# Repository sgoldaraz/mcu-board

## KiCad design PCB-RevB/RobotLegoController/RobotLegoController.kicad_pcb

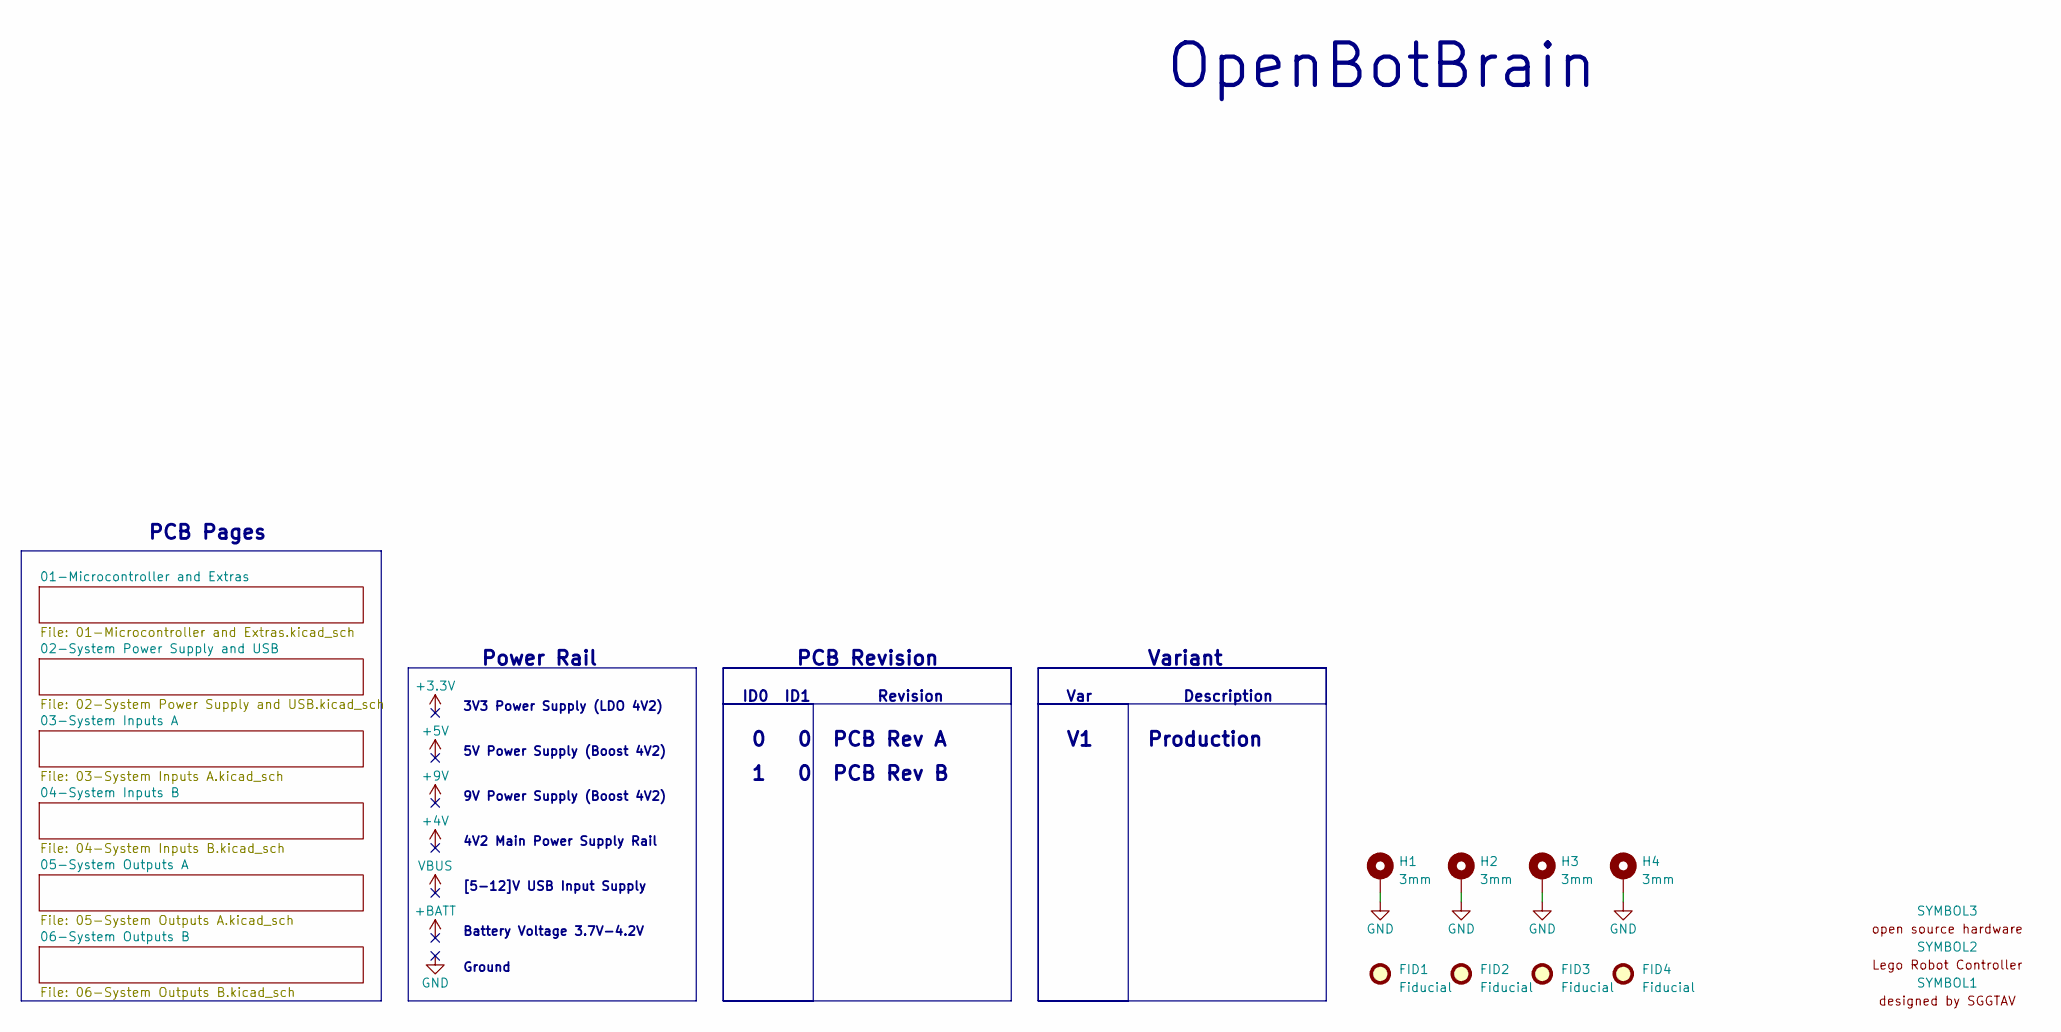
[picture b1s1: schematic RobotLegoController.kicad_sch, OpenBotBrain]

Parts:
FID1, FID2, FID3, FID4: Fiducial; Fiducial_1mm_Mask3mm
H1, H2, H3, H4: 3mm; MountingHole_3.2mm_M3_Pad
SYMBOL1: sggtav_logo
SYMBOL2: lego_robot_controller
SYMBOL3: open_source

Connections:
GND: H1.1, H2.1, H3.1, H4.1; also elsewhere on the board

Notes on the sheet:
Power Rail
Var
0 0
ID0 ID1
9V Power Supply (Boost 4V2)
3V3 Power Supply (LDO 4V2)
Battery Voltage 3.7V-4.2V
PCB Rev B
Variant
[5-12]V USB Input Supply
Description
1 0
Production
PCB Revision
PCB Rev A
4V2 Main Power Supply Rail
Revision
PCB Pages
Ground
5V Power Supply (Boost 4V2)
OpenBotBrain

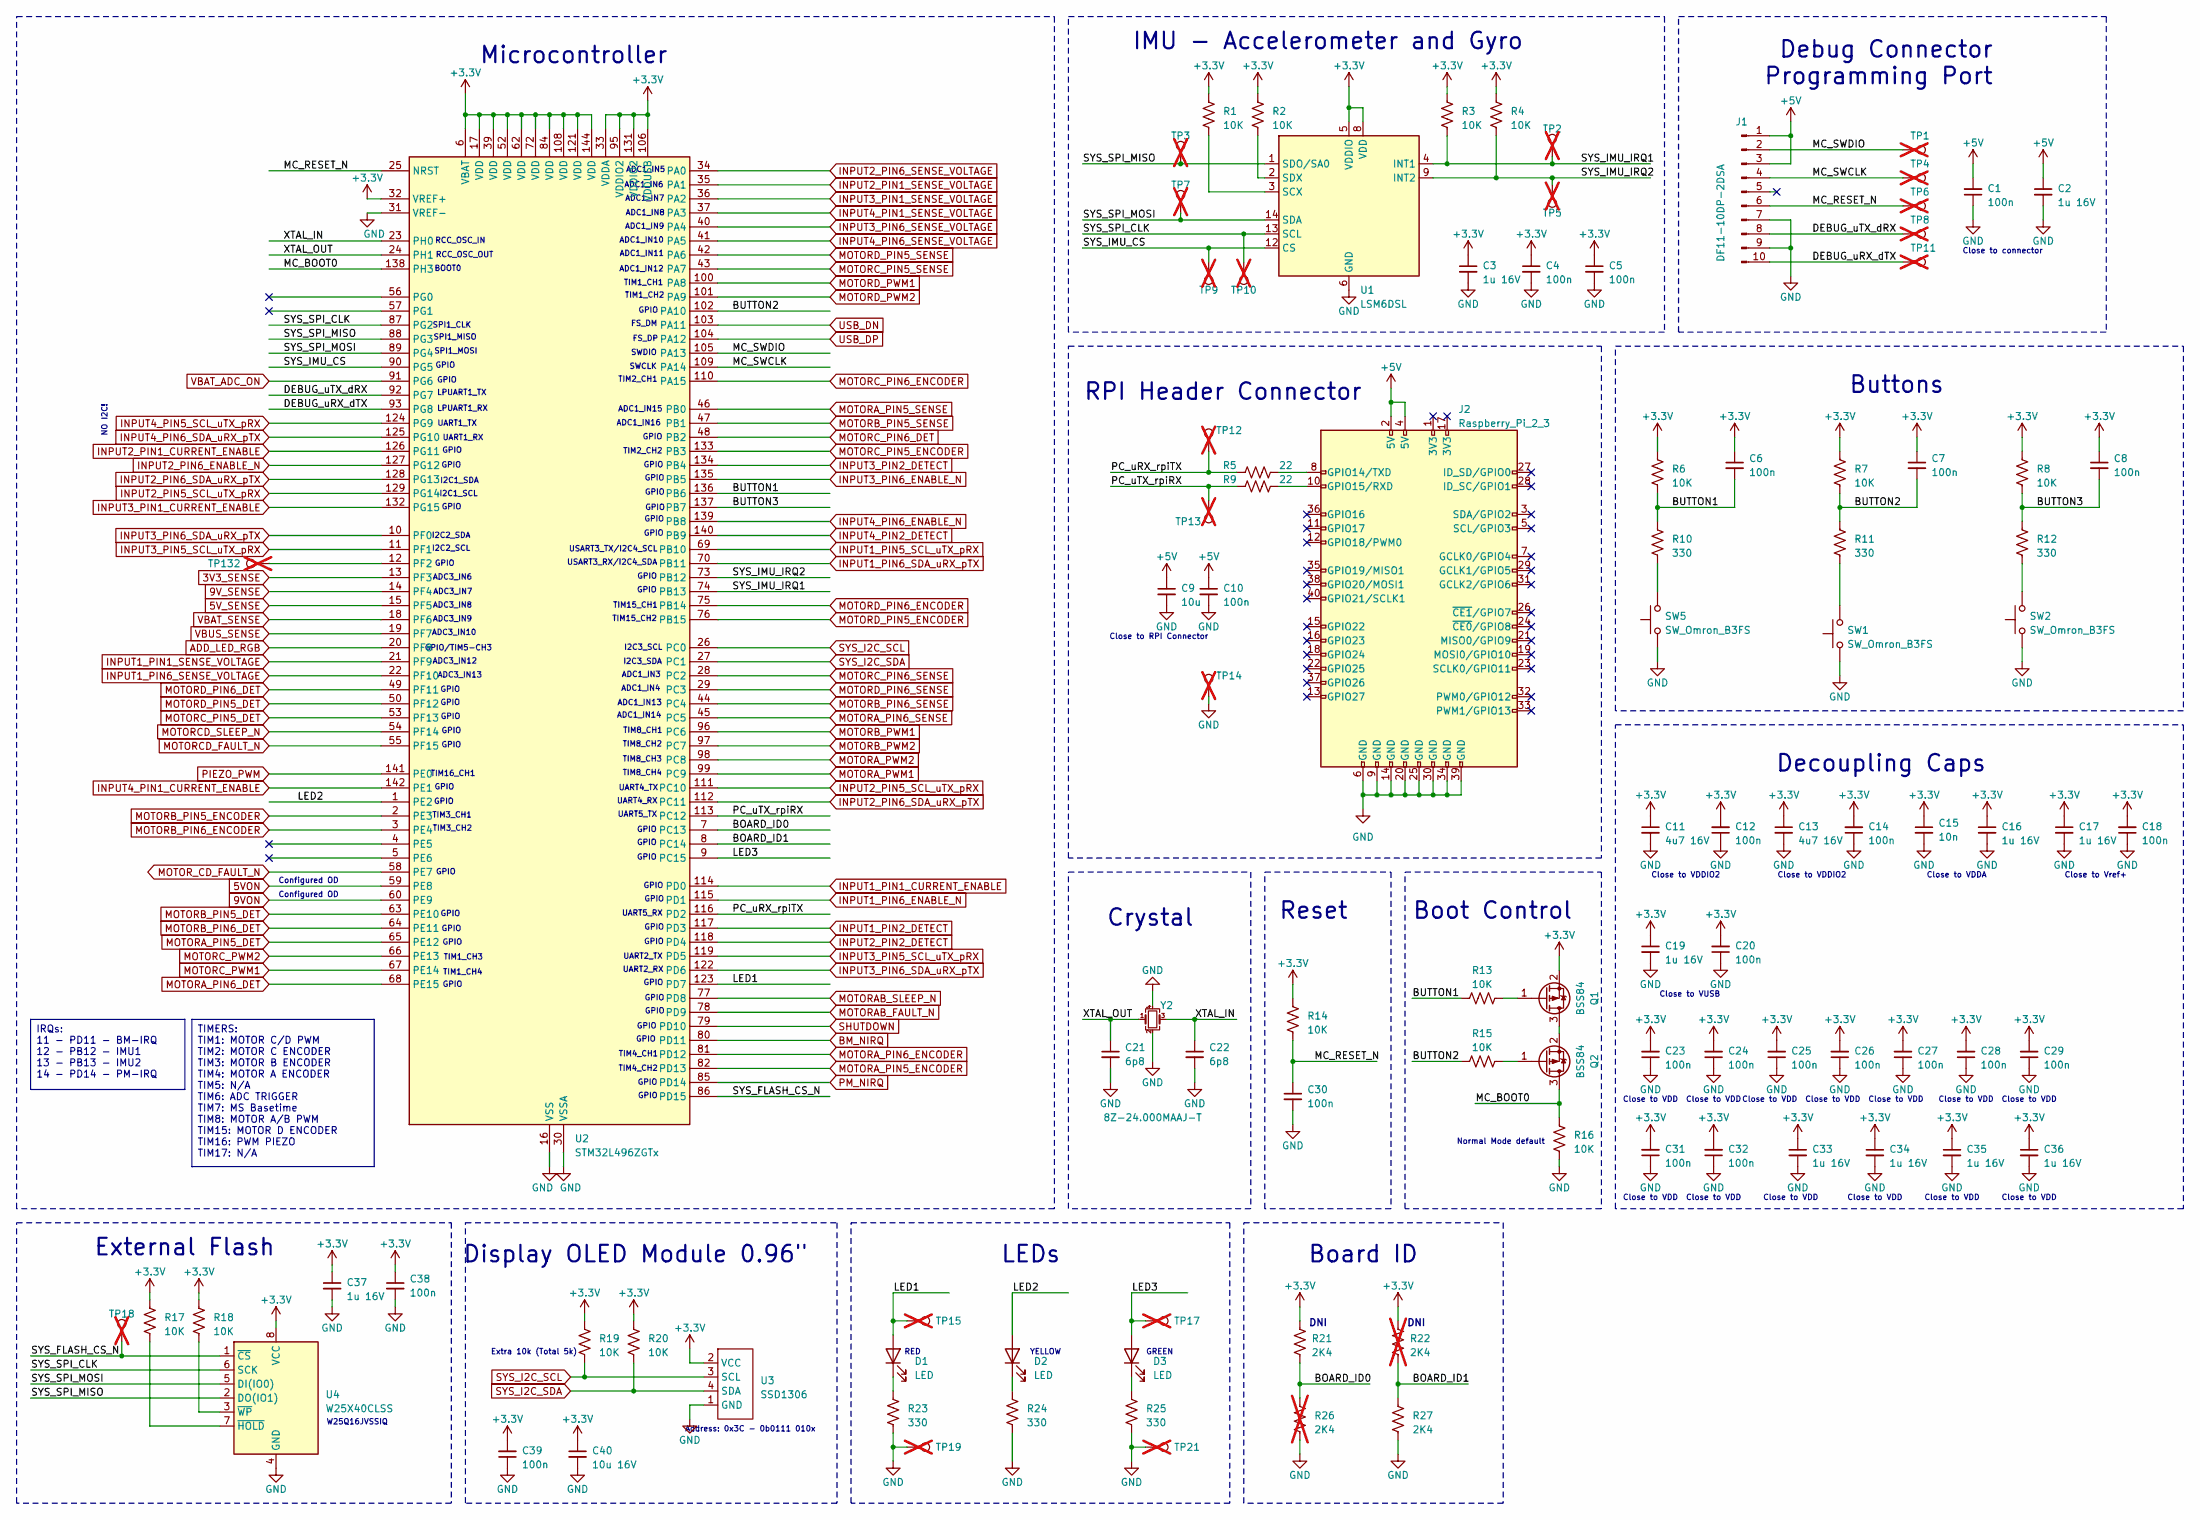
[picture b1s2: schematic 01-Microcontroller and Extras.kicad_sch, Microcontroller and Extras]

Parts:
C1, C4, C5, C6, C7, C8, C10, C12, C14, C18, C20, C23, C24, C25, C26, C27, C28, C29, C30, C31, C32, C38, C39: 100n; C_0402_1005Metric
C2, C3, C16, C17, C19, C33, C34, C35, C36, C37: 1u 16V; C_0603_1608Metric
C9: 10u; C_0805_2012Metric
C11, C13: 4u7 16V; C_0603_1608Metric
C15: 10n; C_0402_1005Metric
C21, C22: 6p8; C_0402_1005Metric
C40: 10u 16V; C_0805_2012Metric
D1, D2, D3: LED; LED_0402_1005Metric
J1: DF11-10DP-2DSA; JST_PHD_B10B-PHDSS_2x05_P2.00mm_Vertical
J2: Raspberry_Pi_2_3; PinHeader_2x20_P2.54mm_Vertical
Q1, Q2: BSS84; SOT-23
R1, R2, R3, R4, R6, R7, R8, R13, R14, R15, R16, R17, R18, R19, R20: 10K; R_0402_1005Metric
R5, R9: 22; R_0402_1005Metric
R10, R11, R12, R23, R24, R25: 330; R_0402_1005Metric
R21, R27: 2K4; R_0402_1005Metric
R22, R26: 2K4; R_0402_1005Metric; not fitted
SW1, SW2, SW5: SW_Omron_B3FS; SW_Push_1P1T_NO_6x6mm_H9.5mm
TP1, TP2, TP3, TP4, TP5, TP6, TP7, TP8, TP9, TP10, TP11, TP12, TP13, TP14, TP18, TP132: S1mm; TestPoint_Pad_1.0x1.0mm; not fitted
TP15, TP17, TP19, TP21: TH1mm; TestPoint_THTPad_1.0x1.0mm_Drill0.5mm; not fitted
U1: LSM6DSL; LGA-14_3x2.5mm_P0.5mm_LayoutBorder3x4y
U2: STM32L496ZGTx; LQFP-144_20x20mm_P0.5mm
U3: SSD1306; 128x64OLED
U4: W25X40CLSS; SOIC-8_5.275x5.275mm_P1.27mm
Y2: 8Z-24.000MAAJ-T; Crystal_SMD_Abracon_ABM10-4Pin_2.5x2.0mm

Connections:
3V3_SENSE: U2.13 (PF3); also elsewhere on the board
5VON: U2.59 (PE8); also elsewhere on the board
5V_SENSE: U2.15 (PF5); also elsewhere on the board
9VON: U2.60 (PE9); also elsewhere on the board
9V_SENSE: U2.14 (PF4); also elsewhere on the board
+3.3V: C3.1, C4.1, C5.1, C6.1, C7.1, C8.1, C11.1, C12.2, C13.1, C14.2, C15.1, C16.1, C17.1, C18.2, C19.1, C20.2, C23.2, C24.2, C25.2, C26.2, C27.2, C28.2, C29.2, C31.2, C32.2, C33.1, C34.1, C35.1, C36.1, C37.1, C38.1, C39.2, C40.1, Q1.2 (S), R1.2, R2.2, R3.2, R4.2, R6.2, R7.2, R8.2, R14.2, R17.2, R18.2, R19.2, R20.2, R21.2, R22.2, U1.5 (VDDIO), U1.8 (VDD), U2.6 (VBAT), U2.17 (VDD), U2.32 (VREF+), U2.33 (VDDA), U2.39 (VDD), U2.52 (VDD), U2.62 (VDD), U2.72 (VDD), U2.84 (VDD), U2.95 (VDDIO2), U2.106 (VDDUSB), U2.108 (VDD), U2.121 (VDD), U2.131 (VDDIO2), U2.144 (VDD), U3.2 (VCC), U4.8 (VCC); also elsewhere on the board
+5V: C1.2, C2.1, C9.1, C10.1, J1.1, J1.3, J2.2 (5V), J2.4 (5V); also elsewhere on the board
/01-Microcontroller and Extras/BOARD_ID0: R21.1, R26.2, U2.7 (PC13)
/01-Microcontroller and Extras/BOARD_ID1: R22.1, R27.2, U2.8 (PC14)
/01-Microcontroller and Extras/BUTTON1: C6.2, R6.1, R10.2, R13.2, U2.136 (PB6)
/01-Microcontroller and Extras/BUTTON2: C7.2, R7.1, R11.2, R15.2, U2.102 (PA10)
/01-Microcontroller and Extras/BUTTON3: C8.2, R8.1, R12.2, U2.137 (PB7)
/01-Microcontroller and Extras/DEBUG_uRX_dTX: J1.10, TP11.1, U2.93 (PG8)
/01-Microcontroller and Extras/DEBUG_uTX_dRX: J1.8, TP8.1, U2.92 (PG7)
/01-Microcontroller and Extras/LED1: D1.2 (A), TP15.1, U2.123 (PD7)
/01-Microcontroller and Extras/LED2: D2.2 (A), U2.1 (PE2)
/01-Microcontroller and Extras/LED3: D3.2 (A), TP17.1, U2.9 (PC15)
/01-Microcontroller and Extras/MC_BOOT0: Q2.3 (D), R16.1, U2.138 (PH3)
/01-Microcontroller and Extras/MC_RESET_N: C30.1, J1.6, R14.1, TP6.1, U2.25 (NRST)
/01-Microcontroller and Extras/MC_SWCLK: J1.4, TP4.1, U2.109 (PA14)
/01-Microcontroller and Extras/MC_SWDIO: J1.2, TP1.1, U2.105 (PA13)
/01-Microcontroller and Extras/PC_uRX_rpiTX: R5.1, TP12.1, U2.116 (PD2)
/01-Microcontroller and Extras/PC_uTX_rpiRX: R9.1, TP13.1, U2.113 (PC12)
/01-Microcontroller and Extras/SYS_FLASH_CS_N: TP18.1, U2.86 (PD15), U4.1 (~CS)
/01-Microcontroller and Extras/SYS_IMU_CS: TP9.1, U1.12 (CS), U2.90 (PG5)
/01-Microcontroller and Extras/SYS_IMU_IRQ1: R3.1, TP2.1, U1.4 (INT1), U2.74 (PB13)
/01-Microcontroller and Extras/SYS_IMU_IRQ2: R4.1, TP5.1, U1.9 (INT2), U2.73 (PB12)
/01-Microcontroller and Extras/SYS_SPI_CLK: TP10.1, U1.13 (SCL), U2.87 (PG2), U4.6 (SCK)
/01-Microcontroller and Extras/SYS_SPI_MISO: TP3.1, U1.1 (SDO/SA0), U2.88 (PG3), U4.2 (DO(IO1))
/01-Microcontroller and Extras/SYS_SPI_MOSI: TP7.1, U1.14 (SDA), U2.89 (PG4), U4.5 (DI(IO0))
/01-Microcontroller and Extras/XTAL_IN: C22.1, U2.23 (PH0), Y2.3
/01-Microcontroller and Extras/XTAL_OUT: C21.1, U2.24 (PH1), Y2.1
ADD_LED_RGB: U2.20 (PF8); also elsewhere on the board
BM_NIRQ: U2.80 (PD11); also elsewhere on the board
GND: C1.1, C2.2, C3.2, C4.2, C5.2, C9.2, C10.2, C11.2, C12.1, C13.2, C14.1, C15.2, C16.2, C17.2, C18.1, C19.2, C20.1, C21.2, C22.2, C23.1, C24.1, C25.1, C26.1, C27.1, C28.1, C29.1, C30.2, C31.1, C32.1, C33.2, C34.2, C35.2, C36.2, C37.2, C38.2, C39.1, C40.2, J1.7, J1.9, J2.6 (GND), J2.9 (GND), J2.14 (GND), J2.20 (GND), J2.25 (GND), J2.30 (GND), J2.34 (GND), J2.39 (GND), R16.2, R23.1, R24.1, R25.1, R26.1, R27.1, SW1.1, SW2.1, SW5.1, TP14.1, TP19.1, TP21.1, U1.6 (GND), U1.7 (GND), U2.16 (VSS), U2.30 (VSSA), U2.31 (VREF-), U2.38 (VSS), U2.51 (VSS), U2.61 (VSS), U2.71 (VSS), U2.83 (VSS), U2.94 (VSS), U2.107 (VSS), U2.120 (VSS), U2.130 (VSS), U2.143 (VSS), U3.1 (GND), U4.4 (GND), Y2.2, Y2.4; also elsewhere on the board
INPUT1_PIN1_CURRENT_ENABLE: U2.114 (PD0); also elsewhere on the board
INPUT1_PIN1_SENSE_VOLTAGE: U2.21 (PF9); also elsewhere on the board
INPUT1_PIN2_DETECT: U2.117 (PD3); also elsewhere on the board
INPUT1_PIN5_SCL_uTX_pRX: U2.69 (PB10); also elsewhere on the board
INPUT1_PIN6_ENABLE_N: U2.115 (PD1); also elsewhere on the board
INPUT1_PIN6_SDA_uRX_pTX: U2.70 (PB11); also elsewhere on the board
INPUT1_PIN6_SENSE_VOLTAGE: U2.22 (PF10); also elsewhere on the board
INPUT2_PIN1_CURRENT_ENABLE: U2.126 (PG11); also elsewhere on the board
INPUT2_PIN1_SENSE_VOLTAGE: U2.35 (PA1); also elsewhere on the board
INPUT2_PIN2_DETECT: U2.118 (PD4); also elsewhere on the board
INPUT2_PIN5_SCL_uTX_pRX: U2.111 (PC10), U2.129 (PG14); also elsewhere on the board
INPUT2_PIN6_ENABLE_N: U2.127 (PG12); also elsewhere on the board
INPUT2_PIN6_SDA_uRX_pTX: U2.112 (PC11), U2.128 (PG13); also elsewhere on the board
INPUT2_PIN6_SENSE_VOLTAGE: U2.34 (PA0); also elsewhere on the board
INPUT3_PIN1_CURRENT_ENABLE: U2.132 (PG15); also elsewhere on the board
INPUT3_PIN1_SENSE_VOLTAGE: U2.36 (PA2); also elsewhere on the board
INPUT3_PIN2_DETECT: U2.134 (PB4); also elsewhere on the board
INPUT3_PIN5_SCL_uTX_pRX: U2.11 (PF1), U2.119 (PD5); also elsewhere on the board
INPUT3_PIN6_ENABLE_N: U2.135 (PB5); also elsewhere on the board
INPUT3_PIN6_SDA_uRX_pTX: U2.10 (PF0), U2.122 (PD6); also elsewhere on the board
INPUT3_PIN6_SENSE_VOLTAGE: U2.40 (PA4); also elsewhere on the board
INPUT4_PIN1_CURRENT_ENABLE: U2.142 (PE1); also elsewhere on the board
INPUT4_PIN2_DETECT: U2.140 (PB9); also elsewhere on the board
INPUT4_PIN5_SCL_uTX_pRX: U2.124 (PG9); also elsewhere on the board
INPUT4_PIN6_ENABLE_N: U2.139 (PB8); also elsewhere on the board
INPUT4_PIN6_SDA_uRX_pTX: U2.125 (PG10); also elsewhere on the board
INPUT4_PIN6_SENSE_VOLTAGE: U2.41 (PA5); also elsewhere on the board
MOTORAB_FAULT_N: U2.78 (PD9); also elsewhere on the board
MOTORAB_SLEEP_N: U2.77 (PD8); also elsewhere on the board
MOTORA_PIN5_DET: U2.65 (PE12); also elsewhere on the board
MOTORA_PIN5_ENCODER: U2.82 (PD13); also elsewhere on the board
MOTORA_PIN6_DET: U2.68 (PE15); also elsewhere on the board
MOTORA_PIN6_ENCODER: U2.81 (PD12); also elsewhere on the board
MOTORA_PWM1: U2.99 (PC9); also elsewhere on the board
MOTORA_PWM2: U2.98 (PC8); also elsewhere on the board
MOTORB_PIN5_DET: U2.63 (PE10); also elsewhere on the board
MOTORB_PIN5_ENCODER: U2.2 (PE3); also elsewhere on the board
MOTORB_PIN6_DET: U2.64 (PE11); also elsewhere on the board
MOTORB_PIN6_ENCODER: U2.3 (PE4); also elsewhere on the board
MOTORB_PWM1: U2.96 (PC6); also elsewhere on the board
MOTORB_PWM2: U2.97 (PC7); also elsewhere on the board
MOTORCD_FAULT_N: U2.55 (PF15)
MOTORCD_SLEEP_N: U2.54 (PF14); also elsewhere on the board
MOTORC_PIN5_DET: U2.53 (PF13); also elsewhere on the board
MOTORC_PIN5_ENCODER: U2.133 (PB3); also elsewhere on the board
MOTORC_PIN5_SENSE: U2.43 (PA7); also elsewhere on the board
MOTORC_PIN6_DET: U2.48 (PB2); also elsewhere on the board
MOTORC_PIN6_ENCODER: U2.110 (PA15); also elsewhere on the board
MOTORC_PIN6_SENSE: U2.28 (PC2); also elsewhere on the board
MOTORC_PWM1: U2.67 (PE14); also elsewhere on the board
MOTORC_PWM2: U2.66 (PE13); also elsewhere on the board
MOTORD_PIN5_DET: U2.50 (PF12); also elsewhere on the board
MOTORD_PIN5_ENCODER: U2.76 (PB15); also elsewhere on the board
MOTORD_PIN5_SENSE: U2.42 (PA6); also elsewhere on the board
MOTORD_PIN6_DET: U2.49 (PF11); also elsewhere on the board
MOTORD_PIN6_ENCODER: U2.75 (PB14); also elsewhere on the board
MOTORD_PIN6_SENSE: U2.29 (PC3); also elsewhere on the board
MOTORD_PWM1: U2.100 (PA8); also elsewhere on the board
MOTORD_PWM2: U2.101 (PA9); also elsewhere on the board
MOTOR_CD_FAULT_N: U2.58 (PE7); also elsewhere on the board
unnamed: D1.1 (K), R23.2
unnamed: D2.1 (K), R24.2
unnamed: D3.1 (K), R25.2
unnamed: J2.8 (GPIO14/TXD), R5.2
unnamed: J2.10 (GPIO15/RXD), R9.2
unnamed: Q1.3 (D), Q2.2 (S)
unnamed: Q1.1 (G), R13.1
unnamed: Q2.1 (G), R15.1
unnamed: R10.1, SW5.2
unnamed: R11.1, SW1.2
unnamed: R12.1, SW2.2
unnamed: R1.1, U1.3 (SCX)
unnamed: R2.1, U1.2 (SDX)
unnamed: TP132.1, U2.12 (PF2)
unnamed: R17.1, U4.7 (~HOLD)
unnamed: R18.1, U4.3 (~WP)
PIEZO_PWM: U2.141 (PE0); also elsewhere on the board
PM_NIRQ: U2.85 (PD14); also elsewhere on the board
SHUTDOWN: U2.79 (PD10); also elsewhere on the board
SYS_I2C_SCL: R19.1, U2.26 (PC0), U3.3 (SCL); also elsewhere on the board
SYS_I2C_SDA: R20.1, U2.27 (PC1), U3.4 (SDA); also elsewhere on the board
USB_DN: U2.103 (PA11); also elsewhere on the board
USB_DP: U2.104 (PA12); also elsewhere on the board
VBAT_ADC_ON: U2.91 (PG6); also elsewhere on the board
VBAT_SENSE: U2.18 (PF6); also elsewhere on the board
VBUS_SENSE: U2.19 (PF7); also elsewhere on the board

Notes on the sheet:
TIM15_CH1
RCC_OSC_IN
I2C3_SDA
TIM2_CH1
SWDIO
Close to connector
Buttons
Display OLED Module 0.96"
GPIO
ADC1_IN16
ADC1_IN13
UART1_RX
UART2_RX
ADC1_IN3
RCC_OSC_OUT
ADC3_IN7
TIM1_CH4
Address: 0x3C - 0b0111 010x
TIM8_CH1
TIM8_CH3
Close to VDD
Close to RPI Connector
USART3_TX/I2C4_SCL
External Flash
Configured OD
UART5_TX
TIM1_CH3
Close to VUSB
UART2_TX
DNI
I2C2_SCL
SWCLK
ADC1_IN5
UART5_RX
LPUART1_TX
ADC1_IN10
W25Q16JVSSIQ
Boot Control
FS_DP
USART3_RX/I2C4_SDA

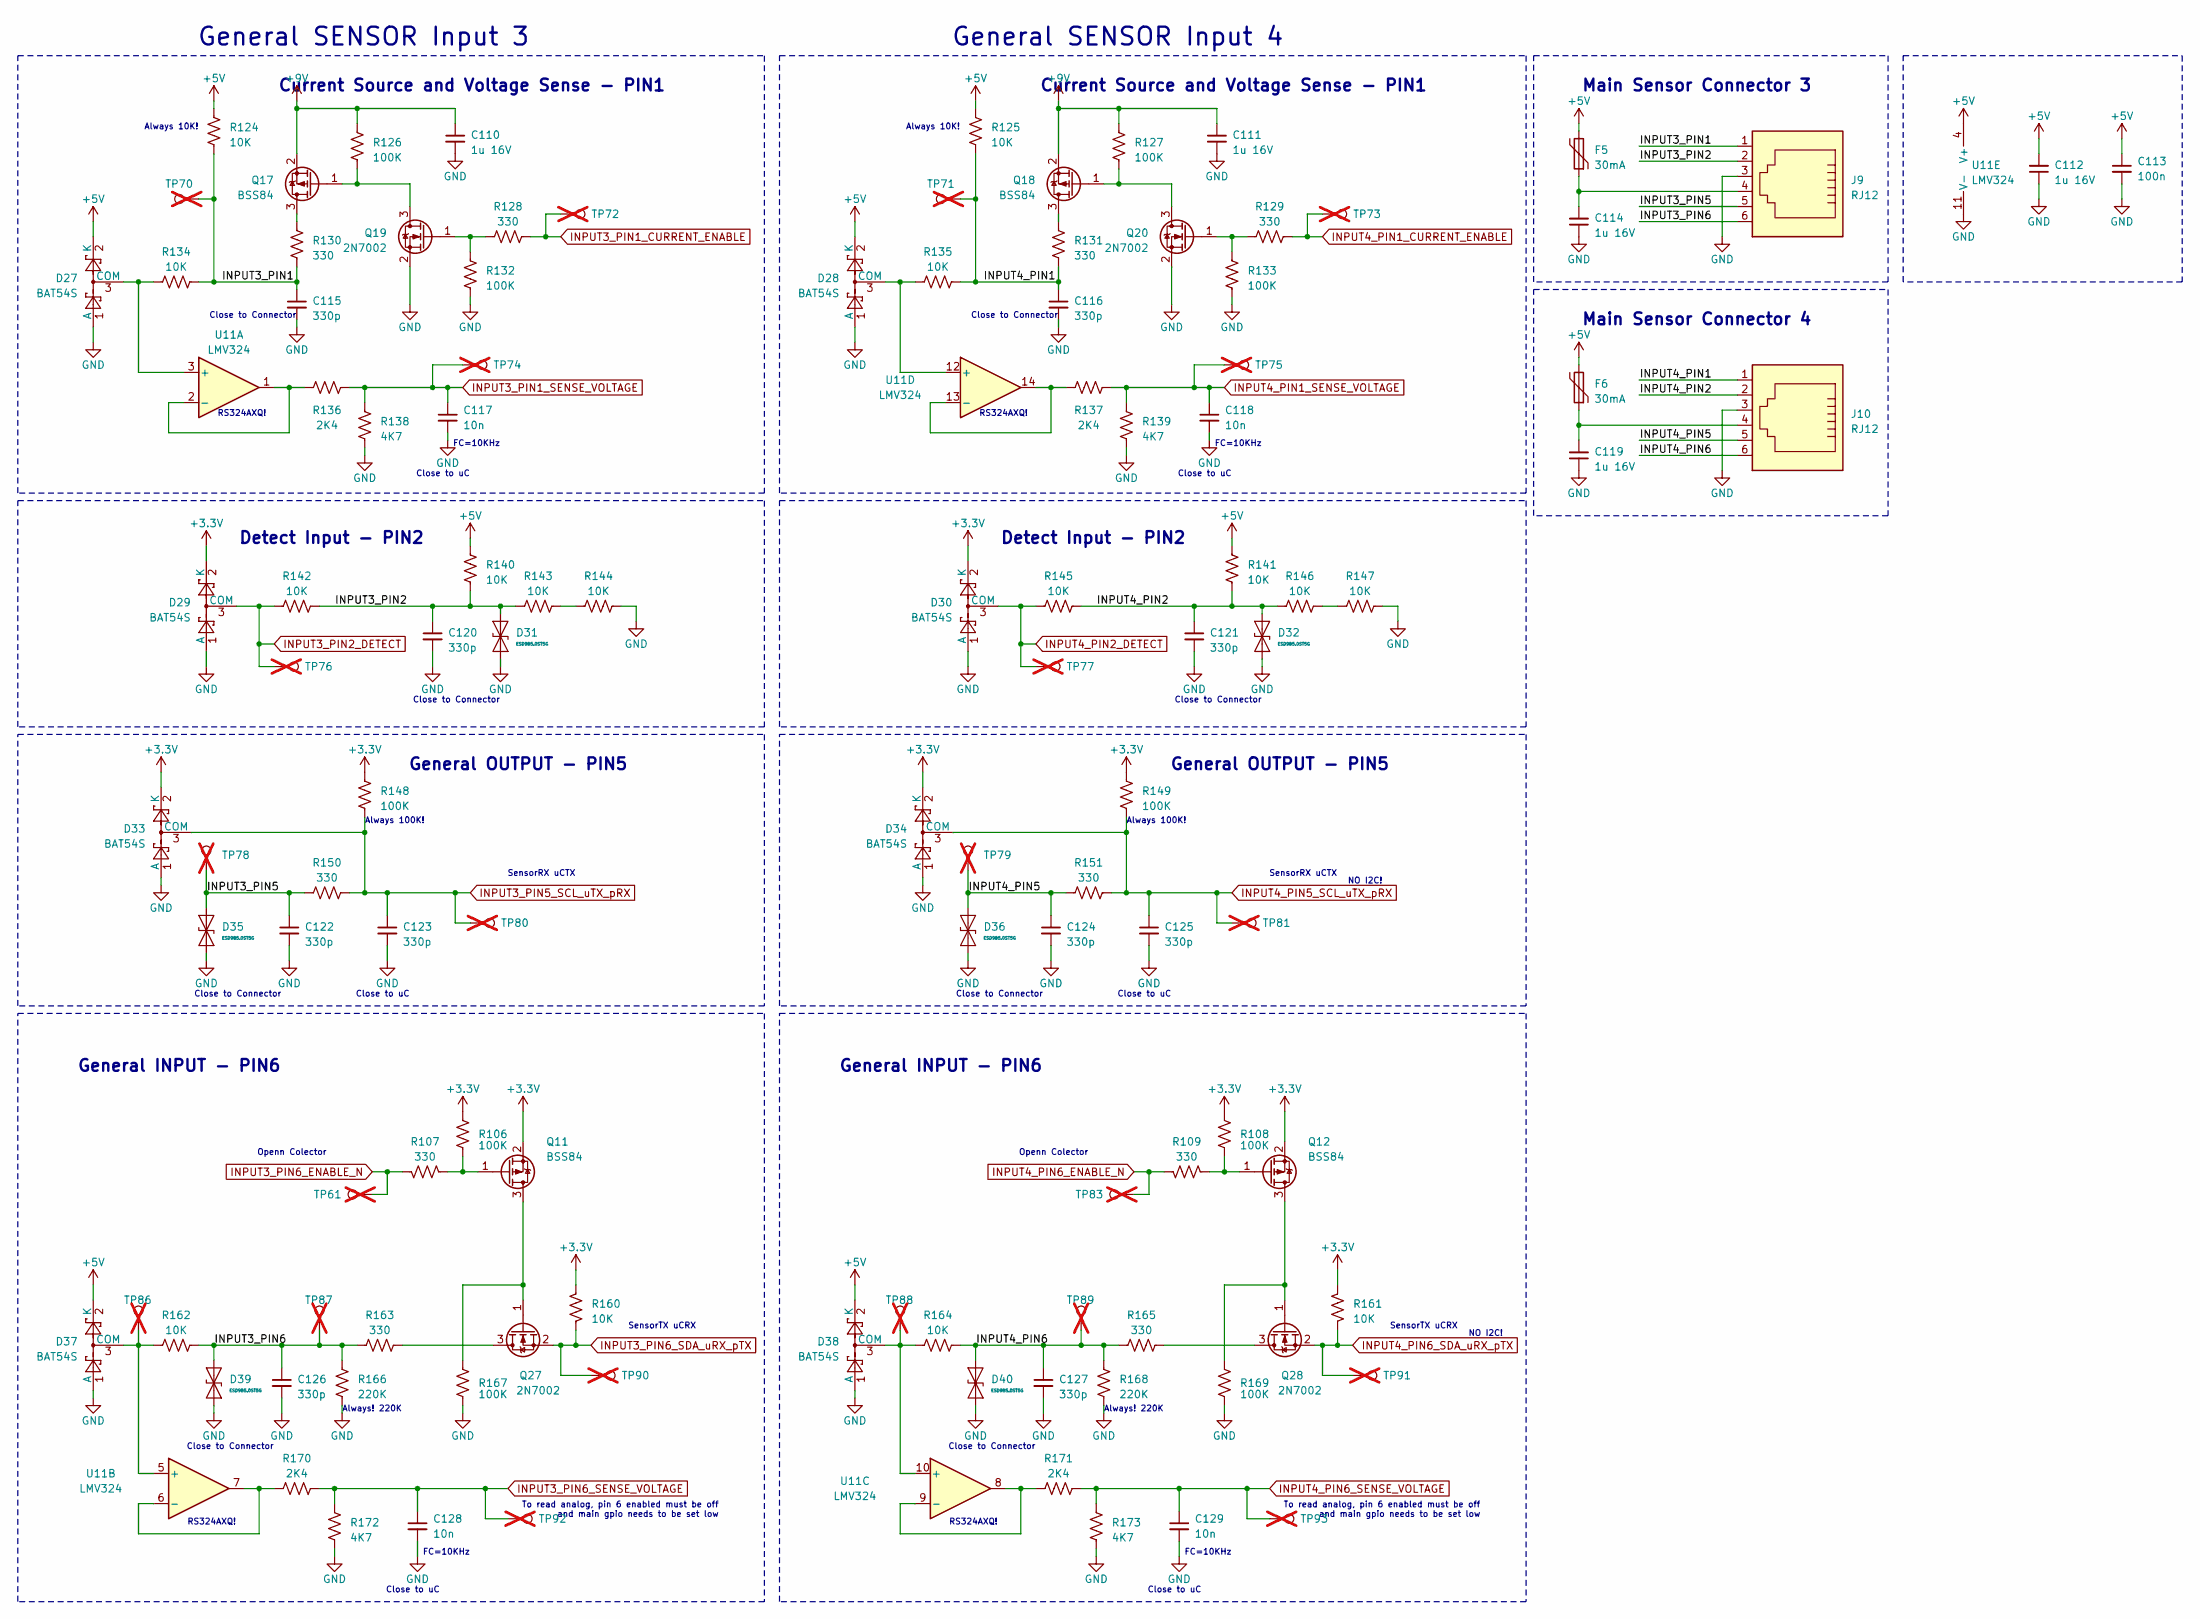
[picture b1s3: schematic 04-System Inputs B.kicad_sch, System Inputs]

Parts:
C110, C111, C112, C114, C119: 1u 16V; C_0603_1608Metric
C113: 100n; C_0402_1005Metric
C115, C116, C120, C121, C122, C123, C124, C125, C126, C127: 330p; C_0402_1005Metric
C117, C118, C128, C129: 10n; C_0402_1005Metric
D27, D28, D29, D30, D33, D34, D37, D38: BAT54S; SOT-23
D31, D32, D35, D36, D39, D40: ESD9B5.0ST5G; D_SOD-923
F5, F6: 30mA; R_0603_1608Metric
J9, J10: RJ12; RJ25_Wayconn_MJEA-660X1_Horizontal
Q11, Q12, Q17, Q18: BSS84; SOT-23
Q19, Q20, Q27, Q28: 2N7002; SOT-23
R106, R108, R126, R127, R132, R133, R148, R149, R167, R169: 100K; R_0402_1005Metric
R107, R109, R128, R129, R130, R131, R150, R151, R163, R165: 330; R_0402_1005Metric
R124, R125, R134, R135, R140, R141, R142, R143, R144, R145, R146, R147, R160, R161, R162, R164: 10K; R_0402_1005Metric
R136, R137, R170, R171: 2K4; R_0402_1005Metric
R138, R139, R172, R173: 4K7; R_0402_1005Metric
R166, R168: 220K; R_0402_1005Metric
TP61, TP70, TP71, TP72, TP73, TP74, TP75, TP76, TP77, TP78, TP79, TP80, TP81, TP83, TP86, TP87, TP88, TP89, TP90, TP91, TP92, TP93: S1mm; TestPoint_Pad_1.0x1.0mm; not fitted
U11: LMV324; SOIC-14_3.9x8.7mm_P1.27mm

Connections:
+3.3V: D29.2 (K), D30.2 (K), D33.2 (K), D34.2 (K), Q11.2 (S), Q12.2 (S), R106.2, R108.2, R148.2, R149.2, R160.1, R161.1; also elsewhere on the board
+5V: C112.2, C113.1, D27.2 (K), D28.2 (K), D37.2 (K), D38.2 (K), F5.2, F6.2, R124.2, R125.2, R140.2, R141.2, U11.4 (V+); also elsewhere on the board
+9V: C110.1, C111.1, Q17.2 (S), Q18.2 (S), R126.2, R127.2; also elsewhere on the board
/04-System Inputs B/INPUT3_PIN1: C115.1, J9.1, R124.1, R130.1, R134.1, TP70.1
/04-System Inputs B/INPUT3_PIN2: C120.1, D31.2 (A2), J9.2, R140.1, R142.2, R143.2
/04-System Inputs B/INPUT3_PIN5: C122.1, D35.2 (A2), J9.5, R150.2, TP78.1
/04-System Inputs B/INPUT3_PIN6: C126.1, D39.2 (A2), J9.6, R162.2, R163.2, R166.1, TP87.1
/04-System Inputs B/INPUT4_PIN1: C116.1, J10.1, R125.1, R131.1, R135.1, TP71.1
/04-System Inputs B/INPUT4_PIN2: C121.1, D32.2 (A2), J10.2, R141.1, R145.2, R146.2
/04-System Inputs B/INPUT4_PIN5: C124.1, D36.2 (A2), J10.5, R151.2, TP79.1
/04-System Inputs B/INPUT4_PIN6: C127.1, D40.2 (A2), J10.6, R164.2, R165.2, R168.1, TP89.1
GND: C110.2, C111.2, C112.1, C113.2, C114.1, C115.2, C116.2, C117.2, C118.2, C119.1, C120.2, C121.2, C122.2, C123.2, C124.2, C125.2, C126.2, C127.2, C128.2, C129.2, D27.1 (A), D28.1 (A), D29.1 (A), D30.1 (A), D31.1 (A1), D32.1 (A1), D33.1 (A), D34.1 (A), D35.1 (A1), D36.1 (A1), D37.1 (A), D38.1 (A), D39.1 (A1), D40.1 (A1), J9.3, J10.3, Q19.2 (S), Q20.2 (S), R132.1, R133.1, R138.2, R139.2, R144.1, R147.1, R166.2, R167.1, R168.2, R169.1, R172.2, R173.2, U11.11 (V-); also elsewhere on the board
INPUT3_PIN1_CURRENT_ENABLE: R128.1, TP72.1; also elsewhere on the board
INPUT3_PIN1_SENSE_VOLTAGE: C117.1, R136.2, R138.1, TP74.1; also elsewhere on the board
INPUT3_PIN2_DETECT: D29.3 (COM), R142.1, TP76.1; also elsewhere on the board
INPUT3_PIN5_SCL_uTX_pRX: C123.1, D33.3 (COM), R148.1, R150.1, TP80.1; also elsewhere on the board
INPUT3_PIN6_ENABLE_N: R107.1, TP61.1; also elsewhere on the board
INPUT3_PIN6_SDA_uRX_pTX: Q27.2 (S), R160.2, TP90.1; also elsewhere on the board
INPUT3_PIN6_SENSE_VOLTAGE: C128.1, R170.2, R172.1, TP92.1; also elsewhere on the board
INPUT4_PIN1_CURRENT_ENABLE: R129.1, TP73.1; also elsewhere on the board
INPUT4_PIN2_DETECT: D30.3 (COM), R145.1, TP77.1; also elsewhere on the board
INPUT4_PIN5_SCL_uTX_pRX: C125.1, D34.3 (COM), R149.1, R151.1, TP81.1; also elsewhere on the board
INPUT4_PIN6_ENABLE_N: R109.1, TP83.1; also elsewhere on the board
INPUT4_PIN6_SDA_uRX_pTX: Q28.2 (S), R161.2, TP91.1; also elsewhere on the board
INPUT4_PIN6_SENSE_VOLTAGE: C129.1, R171.2, R173.1, TP93.1; also elsewhere on the board
unnamed: C114.2, F5.1, J9.4
unnamed: C119.2, F6.1, J10.4
unnamed: D27.3 (COM), R134.2, U11.3 (+)
unnamed: D28.3 (COM), R135.2, U11.12 (+)
unnamed: D37.3 (COM), R162.1, TP86.1, U11.5 (+)
unnamed: D38.3 (COM), R164.1, TP88.1, U11.10 (+)
unnamed: Q11.3 (D), Q27.1 (G), R167.2
unnamed: Q11.1 (G), R106.1, R107.2
unnamed: Q12.3 (D), Q28.1 (G), R169.2
unnamed: Q12.1 (G), R108.1, R109.2
unnamed: Q17.3 (D), R130.2
unnamed: Q17.1 (G), Q19.3 (D), R126.1
unnamed: Q18.3 (D), R131.2
unnamed: Q18.1 (G), Q20.3 (D), R127.1
unnamed: Q19.1 (G), R128.2, R132.2
unnamed: Q20.1 (G), R129.2, R133.2
unnamed: Q27.3 (D), R163.1
unnamed: Q28.3 (D), R165.1
unnamed: R143.1, R144.2
unnamed: R146.1, R147.2
unnamed: R136.1, U11.1, U11.2 (-)
unnamed: R170.1, U11.6 (-), U11.7
unnamed: R171.1, U11.8, U11.9 (-)
unnamed: R137.1, U11.13 (-), U11.14

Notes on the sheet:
Always 10K!
Openn Colector
General SENSOR Input 3
General OUTPUT - PIN5
FC=10KHz
Close to uC
SensorTX uCRX
Close to Connector
RS324AXQ!
SensorRX uCTX
Current Source and Voltage Sense - PIN1
NO I2C!
To read analog, pin 6 enabled must be off and main gpio needs to be set low
Always 100K!
General SENSOR Input 4
Detect Input - PIN2
Always! 220K
Main Sensor Connector 4
General INPUT - PIN6
Main Sensor Connector 3
